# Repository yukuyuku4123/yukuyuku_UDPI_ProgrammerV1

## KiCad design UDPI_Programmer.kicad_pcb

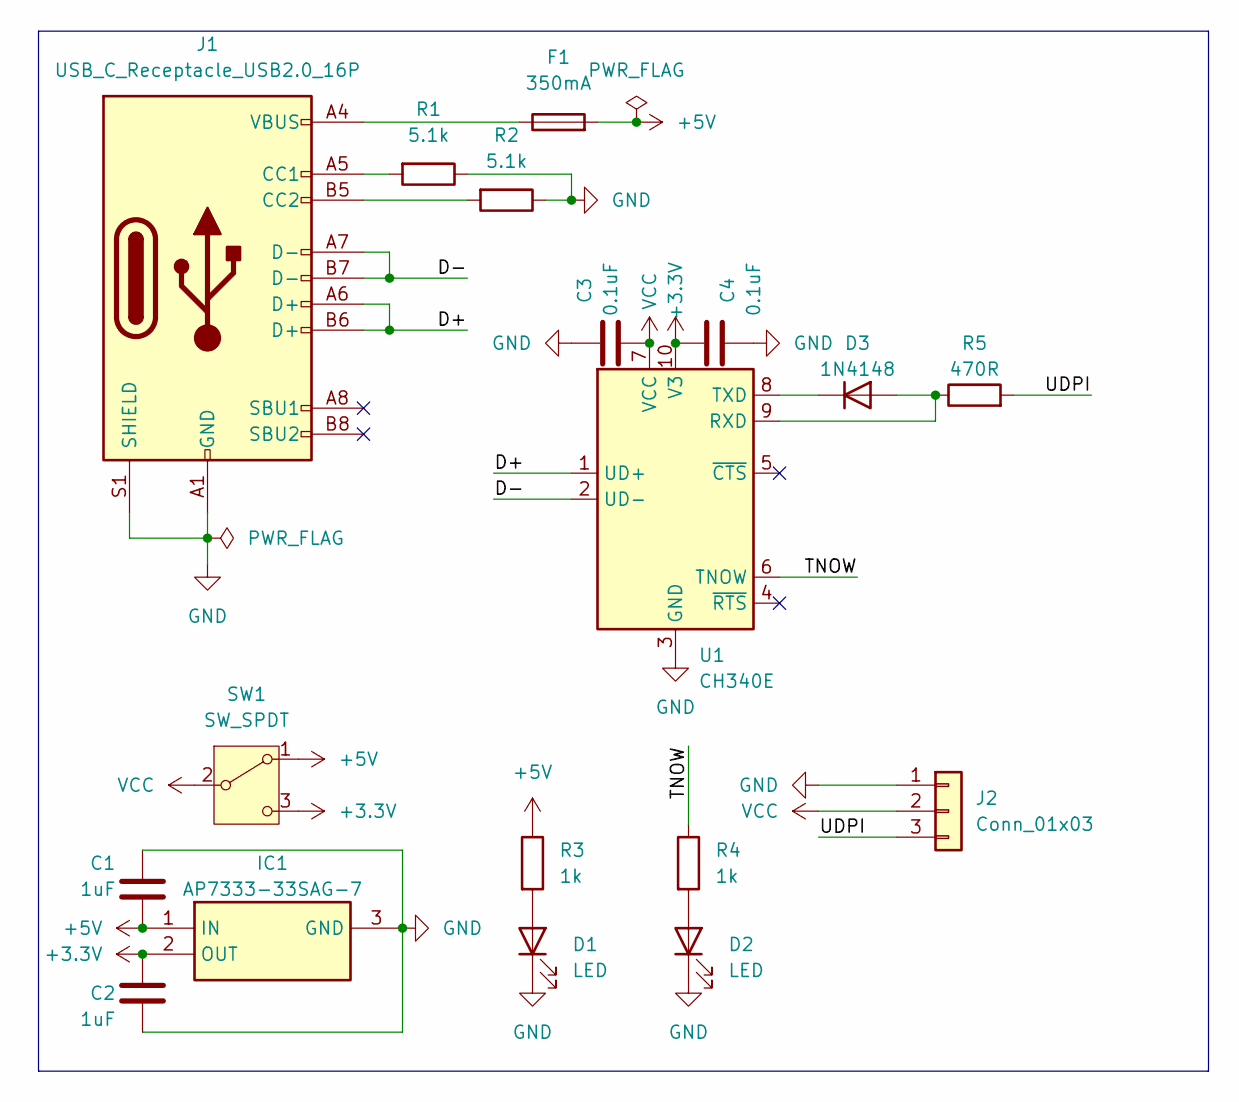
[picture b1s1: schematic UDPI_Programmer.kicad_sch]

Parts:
C1, C2: 1uF; C_0603_1608Metric
C3, C4: 0.1uF; C_0402_1005Metric
D1, D2: LED; LED_0603_1608Metric
D3: 1N4148; D_SOD-123
F1: 350mA; Fuse_0402_1005Metric
IC1: AP7333-33SAG-7; TSOT-23; Mouser Part Number 621-AP7333-33SAG-7
J1: USB_C_Receptacle_USB2.0_16P; USB_C_Receptacle_GCT_USB4105-xx-A_16P_TopMnt_Horizontal
J2: Conn_01x03; PinHeader_1x03_P2.54mm_Vertical
R1, R2: 5.1k; R_0603_1608Metric
R3, R4: 1k; R_0603_1608Metric
R5: 470R; R_0603_1608Metric
SW1: SW_SPDT; SW_Slide_SPDT_Angled_CK_OS102011MA1Q
U1: CH340E; MSOP-10_3x3mm_P0.5mm

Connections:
+3.3V: C2.1, C4.1, IC1.2 (OUT), SW1.3 (C), U1.10 (V3)
+5V: C1.2, F1.2, IC1.1 (IN), R3.1, SW1.1 (A)
/D+: J1.A6 (D+), J1.B6 (D+), U1.1 (UD+)
/D-: J1.A7 (D-), J1.B7 (D-), U1.2 (UD-)
/TNOW: R4.1, U1.6 (TNOW)
/UDPI: J2.3, R5.2
GND: C1.1, C2.2, C3.1, C4.2, D1.1 (K), D2.1 (K), IC1.3 (GND), J1.A1 (GND), J1.A12 (GND), J1.B1 (GND), J1.B12 (GND), J1.S1 (SHIELD), J2.1, R1.1, R2.1, U1.3 (GND)
unnamed: D1.2 (A), R3.2
unnamed: D2.2 (A), R4.2
unnamed: D3.2 (A), R5.1, U1.9 (RXD)
unnamed: D3.1 (K), U1.8 (TXD)
unnamed: F1.1, J1.A4 (VBUS), J1.A9 (VBUS), J1.B4 (VBUS), J1.B9 (VBUS)
unnamed: J1.A5 (CC1), R1.2
unnamed: J1.B5 (CC2), R2.2
VCC: C3.2, J2.2, SW1.2 (B), U1.7 (VCC)

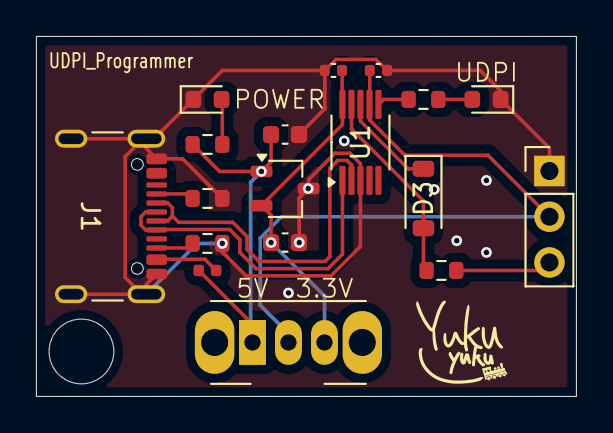
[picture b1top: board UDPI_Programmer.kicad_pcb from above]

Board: 2 copper layers, 30.0 x 20.0 mm, 18 parts (0 on the bottom side), 15 nets.

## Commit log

2024-07-27 Ver-1.0
2024-07-27 Create LICENSE
2024-07-27 Update LICENSE
